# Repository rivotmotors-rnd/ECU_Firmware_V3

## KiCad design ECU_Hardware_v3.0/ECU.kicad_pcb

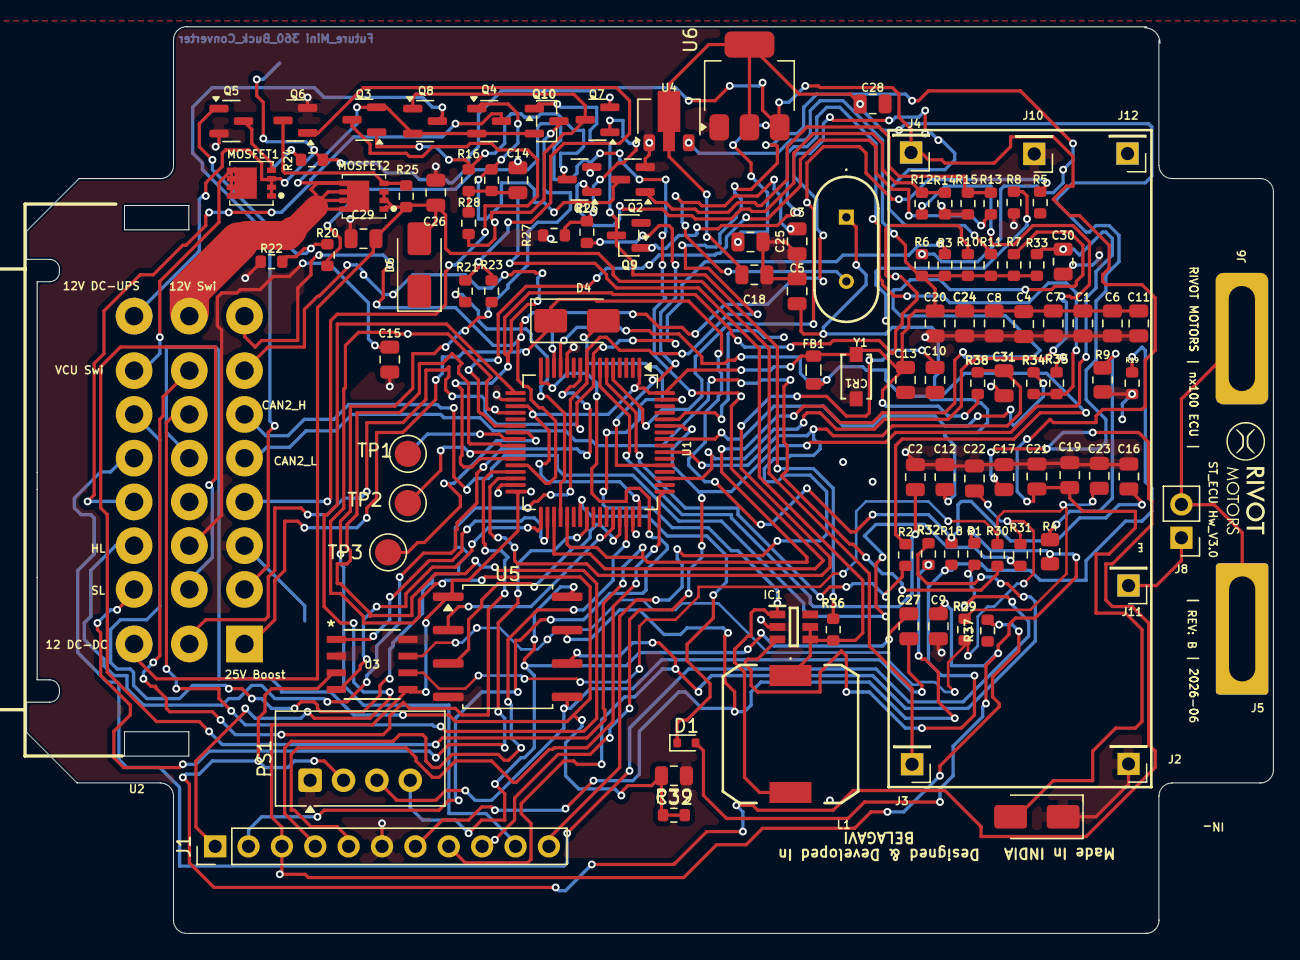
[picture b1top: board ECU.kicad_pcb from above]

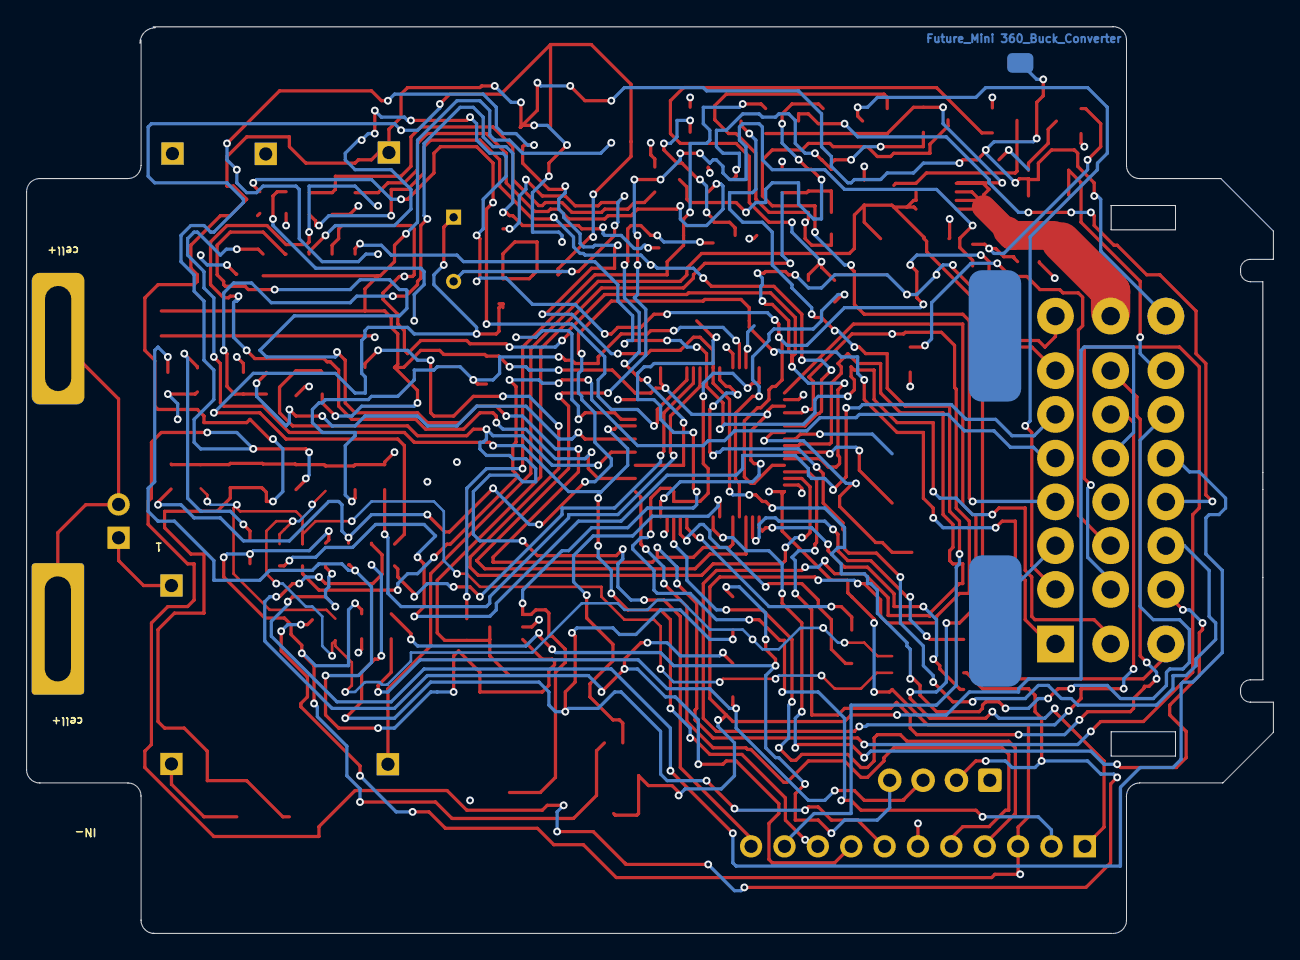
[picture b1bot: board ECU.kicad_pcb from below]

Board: 2 copper layers, 94.9 x 69.0 mm, 114 parts (2 on the bottom side), 78 nets.

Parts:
C1: 10uF; C_0805_2012Metric
C2, C4, C6, C7, C8, C9, C11, C12, C15, C17, C19, C21, C22, C23, C26, C29, C30, C31, C32: 0.1uF; C_0805_2012Metric
C3, C5: 20pF; C_0805_2012Metric
C10: 4.7uF; C_0805_2012Metric
C13: 1uF; C_0805_2012Metric
C14, C16, C18, C20, C25, C28: 22uF; C_0805_2012Metric
C24, C27: 0.1 uF; C_0805_2012Metric
CR1: SMF3.3; CR_SOD-123FL_LTF
D1: 1N4148WT- 1V 50mA; D_SOD-523
D4: SS34; D_SMA
D5, D6: SMAJ13CA; D_SMA
FB1: 600R; L_0805_2012Metric
IC1: MT3608; SOT95P280X145-6N
J1: Conn_01x11; PinHeader_1x11_P2.54mm_Vertical
J2: IN -; PinHeader_1x01_P2.54mm_Vertical
J3: IN +; PinHeader_1x01_P2.54mm_Vertical
J4: DC UPS out; PinHeader_1x01_P2.54mm_Vertical
J5: Cell J1; PinHeader_1x01_P2.54mm_Vertical
J6: Cell J2; PinHeader_1x01_P2.54mm_Vertical
J8: Conn_01x02_Pin; PinHeader_1x02_P2.54mm_Vertical
J10: OUT -; PinHeader_1x01_P2.54mm_Vertical
J11: Bat +; PinHeader_1x01_P2.54mm_Vertical
J12: BAT -; PinHeader_1x01_P2.54mm_Vertical
J13, J14: BAT -; TestPoint_Pad_1.0x1.0mm
L1: 47uH CDRH104RT125NP; CDRH104RT125NP220MC
MOSFET1, MOSFET2: DMP3007SFG-7
PS1: B0505S-1W; Converter_DCDC_TRACO_TBA1-xxxx_THT
Q1, Q2, Q5, Q6, Q7, Q9: AO3400A; SOT-23
Q3, Q4, Q8, Q10: AO3401A; SOT-23
R1, R3, R6, R7, R8, R10, R11, R14, R15, R16, R17, R19, R22, R23, R24, R25, R27, R28, R35, R36: 10K; R_0603_1608Metric
R2, R5: 0R; R_0603_1608Metric
R4: 2.2K; R_0805_2012Metric
R9: 1.5K; R_0805_2012Metric
R12, R13, R20, R21, R26, R34: 1K; R_0603_1608Metric
R18: 390K; R_0603_1608Metric
R29, R32: 120R; R_0603_1608Metric
R30, R31: 0; R_0603_1608Metric
R33, R37, R38: 10k; R_0603_1608Metric
R39: 100; R_0603_1608Metric
TP1, TP2, TP3: TestPoint; TestPoint_Keystone_5000-5004_Miniature
U1: STM32F446RETx; LQFP-64_10x10mm_P0.5mm
U2: 针座灰DJ7241-1.5 2.8-10; CONN-TH_DJ7241-1.5-2.8-10
U3: TJA1051T/3/1J; SO8_SOT96-1_NXP
U4: HT7333-1-SOT89; SOT-89-3
U5: ISO1050DUB; SOP-8_6.62x9.15mm_P2.54mm
U6: AMS1117-5.0; SOT-223-3_TabPin2
Y1: Crystal; X49ST28000F20JGDTD

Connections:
12V DC UPS O/P: C19.2, C21.2, C25.2, D5.2 (A2), J4.1 (Pin_1_1), MOSFET1.1 (S), MOSFET1.2 (S), MOSFET1.3 (S), R24.2, U2.24, U6.3 (VI)
12V DC-DC: C26.2, C29.2, D6.2 (A2), J3.1 (Pin_1_1), MOSFET2.1 (S), MOSFET2.2 (S), MOSFET2.3 (S), R25.2, U2.17
12V_Swi_Con: C14.2, IC1.4 (EN), IC1.5 (IN), L1.1, MOSFET2.5 (D), MOSFET2.6 (D), MOSFET2.7 (D), MOSFET2.8 (D), Q3.2 (S), Q4.2 (S), Q8.2 (S), Q10.2 (S), R16.2, R17.2, R28.2, R36.2, U2.16
+3.3V: C1.2, C4.2, C6.2, C7.2, C8.2, C11.2, C13.2, C20.2, C24.1, CR1.2, FB1.2, J1.3, R3.2, R6.1, R7.2, R10.2, R11.1, R33.1, R37.2, R38.2, U1.1 (VBAT), U1.19 (VDD), U1.32 (VDD), U1.48 (VDD), U1.64 (VDD), U3.5 (VIO), U4.3 (VOUT), U5.1 (VCC1)
+3.3VA: C12.2, FB1.1, U1.13 (VDDA)
+5V: C17.2, C18.2, C28.2, PS1.2 (VIN), U3.3 (VCC), U4.2 (VIN), U6.2 (VO)
/BOOT0: R8.2, U1.60 (BOOT0)
/ESD Protection, TVS diode , low pass filter, 3.3 buck conversion/CAN_N: C23.2, R29.2, R30.1, U3.6 (CANL)
/ESD Protection, TVS diode , low pass filter, 3.3 buck conversion/CAN_P: C22.2, R29.1, R31.1, U3.7 (CANH)
AUX A: C31.2, J1.11, R38.1, U1.55 (PB3)
BAT +: J8.1, J11.1 (Pin_1_1)
Boost_25V_Controller: C16.2, D4.1 (K), R18.1, U2.1
Brake_Regen_IP: C15.2, R37.1, U1.14 (PA0), U2.11
Brake_Regen_Op: C32.2, R39.1, R39.2, U1.20 (PA4), U2.13
Btn_Hazardlight_IP: R7.1, U1.37 (PC6), U2.10
Btn_HighBeam_IP: R1.1, U2.21
Btn_LHIndicator_IP: R3.1, U1.8 (PC0), U2.9
Btn_OffIndicator_IP: R11.2, U1.28 (PB2), U2.8
Btn_RHIndicator_IP: R10.1, U1.27 (PB1), U2.7
Btn_Seatlock_IP: R6.2, U1.9 (PC1), U2.22
CAN1_H: J1.7, R32.1, U5.7 (CANH)
CAN1_L: J1.8, R32.2, U5.6 (CANL)
CAN2_RX: U1.33 (PB12), U3.4 (RXD)
CAN2_TX: U1.34 (PB13), U3.1 (TXD)
CANH: R31.2, U2.6
CANL: R30.2, U2.5
CP Detect_IP: C30.2, J1.9, R33.2, U1.59 (PB7)
CRX1: U1.44 (PA11), U5.2 (RXD)
CTX1: U1.45 (PA12), U5.3 (TXD)
Contactor Pin 12V+: J1.10, Q10.3 (D)
Contactor_Sig_OP: R34.1, U1.57 (PB5)
HndlLock_Sig_OP: U1.10 (PC2), U2.19
LH_Indicator_Sig_Con: Q3.3 (D), U2.4
LH_Indicator_Sig_OP: R12.1, U1.51 (PC10)
MCU_U2DEBUG_RX: J1.1, U1.17 (PA3)
MCU_U2DEBUG_TX: J1.2, U1.16 (PA2)
MCU_UART3_RX: U1.25 (PC5), U2.14
MCU_UART3_TX: U1.29 (PB10), U2.15
unnamed: C3.2, R5.1, Y1.2
unnamed: C5.2, R2.1, Y1.1
unnamed: C9.1, D1.2 (A), R1.2, R4.1
unnamed: D1.1 (K), U1.39 (PC8)
unnamed: D4.2 (A), IC1.1 (SW), L1.2
unnamed: IC1.3 (FB), R18.2, R19.2
unnamed: J5.1 (Pin_1_1), J6.1 (Pin_1_1), J8.2
unnamed: MOSFET1.4 (G), Q5.3 (D), R24.1
unnamed: MOSFET2.4 (G), Q6.3 (D), R25.1
unnamed: C27.2, PS1.3 (0V), U5.5 (GND2)
unnamed: C27.1, PS1.4 (+VO), U5.8 (VCC2)
unnamed: Q1.3 (D), Q3.1 (G), R16.1
unnamed: Q1.1 (G), R12.2, R14.1
unnamed: Q2.3 (D), Q4.1 (G), R17.1
unnamed: Q2.1 (G), R13.2, R15.1
unnamed: Q5.1 (G), R20.2, R22.1
unnamed: Q6.1 (G), R21.2, R23.1
unnamed: Q7.3 (D), Q8.1 (G), R28.1
unnamed: Q7.1 (G), R26.2, R27.1
unnamed: Q9.1 (G), R34.2, R35.1
unnamed: Q9.3 (D), Q10.1 (G), R36.1
unnamed: R4.2, R9.1
unnamed: C2.2, U1.7 (NRST)
unnamed: TP3.1 (1_1), U1.23 (PA7)
unnamed: TP2.1 (1_1), U1.26 (PB0)
unnamed: TP1.1 (1_1), U1.24 (PC4)
unnamed: R5.2, U1.5 (PH0)
unnamed: R2.2, U1.6 (PH1)
unnamed: C10.1, U1.30 (VCAP_1)
OUT -: C1.1, C2.1, C3.1, C4.1, C5.1, C6.1, C7.1, C8.1, C9.2, C10.2, C11.1, C12.1, C13.1, C14.1, C15.1, C16.1, C17.1, C18.1, C19.1, C20.1, C21.1, C22.1, C23.1, C24.2, C25.1, C26.1, C28.1, C29.1, C30.1, C31.1, C32.1, CR1.1, D5.1 (A1), D6.1 (A1), IC1.2 (GND), J1.6, J2.1 (Pin_1_1), J10.1 (Pin_1_1), J12.1 (Pin_1_1), J13.1 (Pin_1_1), J14.1 (Pin_1_1), PS1.1 (GND), Q1.2 (S), Q2.2 (S), Q5.2 (S), Q6.2 (S), Q7.2 (S), Q9.2 (S), R8.1, R9.2, R14.2, R15.2, R19.1, R22.2, R23.2, R27.2, R35.2, U1.12 (VSSA), U1.18 (VSS), U1.31 (VSS), U1.47 (VSS), U1.63 (VSS), U2.3, U3.2 (GND), U3.8 (S), U4.1 (GND), U5.4 (GND1), U6.1 (GND)
RH_Indicator_Sig_Con: Q8.3 (D), U2.2
RH_Indicator_Sig_OP: R26.1, U1.53 (PC12)
SWCLK: J1.5, U1.49 (PA14)
SWIO: J1.4, U1.46 (PA13)
SeatLock_Sig_OP: U1.40 (PC9), U2.18
Switching_12V: R21.1, U1.36 (PB15)
Tail-lamp_Sig_Con: Q4.3 (D), U2.20
Tail-lamp_Sig_OP: R13.1, U1.22 (PA6)
VCU_Sig_Con: MOSFET1.5 (D), MOSFET1.6 (D), MOSFET1.7 (D), MOSFET1.8 (D), U2.23
VCU_Sig_OP: R20.1, U1.35 (PB14)

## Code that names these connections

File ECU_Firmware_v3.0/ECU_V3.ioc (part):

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Mcu.Name=STM32F446R(C-E)Tx
Mcu.Package=LQFP64
Mcu.UserName=STM32F446RETx
PA11.Mode=CAN_Activate
PA11.Signal=CAN1_RX
PA12.Mode=CAN_Activate
PA12.Signal=CAN1_TX
PA13.Mode=Serial_Wire
PA13.Signal=SYS_JTMS-SWDIO
PA14.Mode=Serial_Wire
PA14.Signal=SYS_JTCK-SWCLK
PA0.GPIOParameters=GPIO_PuPd,GPIO_Label
PA0.GPIO_Label=BRAKE_INP
PA0.GPIO_PuPd=GPIO_PULLUP
PA0.Signal=GPIO_Input
PA2.Mode=Asynchronous
PA2.Signal=USART2_TX
PA3.Mode=Asynchronous
PA3.Signal=USART2_RX
PA4.Mode=DAC_OUT1
PA4.Signal=COMP_DAC1_group
PA6.GPIOParameters=GPIO_Label
PA6.GPIO_Label=TAIL_LAMP
PA6.Signal=GPIO_Output
PB1.GPIOParameters=GPIO_PuPd,GPIO_Label
PB1.GPIO_Label=RIGHT_IND_SW
PB1.GPIO_PuPd=GPIO_PULLUP
PB1.Signal=GPIO_Input
PB10.Mode=Asynchronous
PB10.Signal=USART3_TX
PB12.Mode=CAN_Activate
PB12.Signal=CAN2_RX
PB13.Mode=CAN_Activate
PB13.Signal=CAN2_TX
PB14.GPIOParameters=PinState,GPIO_Label
PB14.GPIO_Label=VCU_PWR
PB14.PinState=GPIO_PIN_SET
PB14.Signal=GPIO_Output
PB15.GPIOParameters=PinState,GPIO_Label
PB15.GPIO_Label=AUX_12V_EN
PB15.PinState=GPIO_PIN_RESET
PB15.Signal=GPIO_Output
PB2.GPIOParameters=GPIO_PuPd,GPIO_Label
PB2.GPIO_Label=OFF_INDICATOR_INP
PB2.GPIO_PuPd=GPIO_PULLUP
PB2.Signal=GPIO_Input
PB3.GPIOParameters=GPIO_PuPd,GPIO_Label
PB3.GPIO_Label=CONTACTOR_FEEDBACK
PB3.GPIO_PuPd=GPIO_PULLUP
PB3.Signal=GPIO_Input
PB5.GPIOParameters=GPIO_Label
PB5.GPIO_Label=HV_CONTACTOR
PB5.Signal=GPIO_Output
PB7.GPIOParameters=GPIO_PuPd,GPIO_Label,GPIO_Mode
PB7.GPIO_Label=CP_LINE_DETECT_Pin
PB7.GPIO_Mode=GPIO_MODE_INPUT
PB7.GPIO_PuPd=GPIO_PULLUP
PB7.Signal=GPIO_Input
PC0.GPIOParameters=GPIO_PuPd,GPIO_Label
PC0.GPIO_Label=LEFT_IND_SW
PC0.GPIO_PuPd=GPIO_PULLUP
PC0.Signal=GPIO_Input
PC1.GPIOParameters=GPIO_PuPd,GPIO_Label
PC1.GPIO_Label=SEAT_BTN
PC1.GPIO_PuPd=GPIO_PULLUP
PC1.Signal=GPIO_Input
PC10.GPIOParameters=GPIO_Label
PC10.GPIO_Label=LEFT_IND_LAMP
PC10.Signal=GPIO_Output
PC12.GPIOParameters=GPIO_Label
PC12.GPIO_Label=RIGHT_IND_LAMP
PC12.Signal=GPIO_Output
PC2.GPIOParameters=GPIO_Label
PC2.GPIO_Label=HANDLE_LOCK
PC2.Signal=GPIO_Output
PC5.Mode=Asynchronous
PC5.Signal=USART3_RX
PC6.GPIOParameters=GPIO_PuPd,GPIO_Label
PC6.GPIO_Label=HAZARD_SW
PC6.GPIO_PuPd=GPIO_PULLUP
PC6.Signal=GPIO_Input
PC8.GPIOParameters=GPIO_PuPd,GPIO_Label
PC8.GPIO_Label=HIGH_BEAM_SENSE
PC8.GPIO_PuPd=GPIO_PULLDOWN
PC8.Signal=GPIO_Input
PC9.GPIOParameters=GPIO_Label
PC9.GPIO_Label=SEAT_LOCK
PC9.Signal=GPIO_Output
PH0-OSC_IN.Mode=HSE-External-Oscillator
PH0-OSC_IN.Signal=RCC_OSC_IN
PH1-OSC_OUT.Mode=HSE-External-Oscillator
PH1-OSC_OUT.Signal=RCC_OSC_OUT
RCC.HSE_VALUE=8000000
RCC.SYSCLKFreq_VALUE=90000000
RCC.SYSCLKSource=RCC_SYSCLKSOURCE_PLLCLK
board=custom

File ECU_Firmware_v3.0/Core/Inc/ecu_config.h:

#ifndef ECU_CONFIG_H
#define ECU_CONFIG_H

#include "stm32f4xx_hal.h"

// =============================================================================
// 1. COMMUNICATION BUSES (UART & CAN)
// =============================================================================

// VCU UART (USART3 - Communication with Android VCU)
#define VCU_TX_PIN                  GPIO_PIN_10
#define VCU_TX_PORT                 GPIOB       // PB10
#define VCU_RX_PIN                  GPIO_PIN_5
#define VCU_RX_PORT                 GPIOC       // PC5
#define VCU_UART_AF                 GPIO_AF7_USART3

// Backward-compatibility aliases for VCU UART
#define VCU_TX_Pin                  VCU_TX_PIN
#define VCU_TX_GPIO_Port            VCU_TX_PORT
#define VCU_RX_Pin                  VCU_RX_PIN
#define VCU_RX_GPIO_Port            VCU_RX_PORT

// Debug UART (USART2 - ST-Link Virtual COM Port / Debug printf)
#define DEBUG_UART_TX_PIN           GPIO_PIN_2
#define DEBUG_UART_TX_PORT          GPIOA       // PA2
#define DEBUG_UART_RX_PIN           GPIO_PIN_3
#define DEBUG_UART_RX_PORT          GPIOA       // PA3
#define DEBUG_UART_AF               GPIO_AF7_USART2

// CAN Bus (CAN2 - Vehicle CAN Network)
#define CAN2_RX_PIN                 GPIO_PIN_12
#define CAN2_RX_PORT                GPIOB       // PB12
#define CAN2_TX_PIN                 GPIO_PIN_13
#define CAN2_TX_PORT                GPIOB       // PB13
#define CAN2_AF                     GPIO_AF9_CAN2

// Backward-compatibility aliases for CAN2
#define CAN2_RX_Pin                 CAN2_RX_PIN
#define CAN2_TX_Pin                 CAN2_TX_PIN
#define CAN2_GPIO_Port              CAN2_RX_PORT

// =============================================================================
// 2. POWER & SWITCHING (MOSFET CONTROL)
// =============================================================================

// 12V Main Load Switching MOSFET
#define SWITCHING_12V_PIN           GPIO_PIN_15
#define SWITCHING_12V_PORT          GPIOB       // PB15
#define SWITCHING_12V               SWITCHING_12V_PIN

// 12V VCU Power / Signal MOSFET
#define VCU_SIG_OP_PIN              GPIO_PIN_14
#define VCU_SIG_OP_PORT             GPIOB       // PB14
#define VCU_SIG_OP                  VCU_SIG_OP_PIN

// =============================================================================
// 3. ACTUATORS & LOCKS
// =============================================================================

// Handlebar Steering Lock (Single-wire DWT Pulse Protocol)
#define HNDLLOCK_SIG_OP_PIN         GPIO_PIN_2
#define HNDLLOCK_SIG_OP_PORT        GPIOC       // PC2

// Seat Latch Solenoid (Pulse Actuation)
#define SEATLOCK_SIG_OP_PIN         GPIO_PIN_9
#define SEATLOCK_SIG_OP_PORT        GPIOC       // PC9

// =============================================================================
// 4. LIGHTING OUTPUTS
// =============================================================================

// Left Turn Indicator Lamp
#define LH_INDICATOR_SIG_OP_PIN     GPIO_PIN_10
#define LH_INDICATOR_SIG_OP_PORT    GPIOC       // PC10
#define LH_INDICATOR_SIG_OP         LH_INDICATOR_SIG_OP_PIN

// Right Turn Indicator Lamp
#define RH_INDICATOR_SIG_OP_PIN     GPIO_PIN_12
#define RH_INDICATOR_SIG_OP_PORT    GPIOC       // PC12
#define RH_INDICATOR_SIG_OP         RH_INDICATOR_SIG_OP_PIN

// Tail Lamp / Backlight Output
#define TAIL_LAMP_SIG_OP_PIN        GPIO_PIN_6
#define TAIL_LAMP_SIG_OP_PORT       GPIOA       // PA6
#define TAIL_LAMP_SIG_OP            TAIL_LAMP_SIG_OP_PIN

// =============================================================================
// 5. VEHICLE INPUTS & SWITCHES
// =============================================================================

// Push-to-Off Digital Brake Switch (PA0, internal pull-up)
// Released at rest (contacts closed to GND) -> LOW (0V)
// Pulled / engaged (contacts open, pulled to 3.3V) -> HIGH (3.3V)
#define BRAKE_INP_PIN               GPIO_PIN_0
#define BRAKE_INP_PORT              GPIOA       // PA0
#define BRAKE_INP                   BRAKE_INP_PIN

// Contactor Weld Auxiliary Feedback (PB3, internal pull-up)
// Contactor OPEN: HIGH (safe)
// Contactor CLOSED/WELDED: LOW
#define CONTACTOR_FEEDBACK_PIN      GPIO_PIN_3
#define CONTACTOR_FEEDBACK_PORT     GPIOB       // PB3

// CP Line Gun Detect (PB7, internal pull-up)
// Gun Connected: LOW
// Gun Disconnected: HIGH
#define CP_LINE_DETECT_PIN          GPIO_PIN_7
#define CP_LINE_DETECT_PORT         GPIOB       // PB7

// Left Turn Indicator Switch
#define LEFT_INDICATOR_INP_PIN      GPIO_PIN_0
#define LEFT_INDICATOR_INP_PORT     GPIOC       // PC0
#define LEFT_INDICATOR_INP          LEFT_INDICATOR_INP_PIN

// Right Turn Indicator Switch
#define RIGHT_INDICATOR_INP_PIN     GPIO_PIN_1
#define RIGHT_INDICATOR_INP_PORT    GPIOB       // PB1
#define RIGHT_INDICATOR_INP         RIGHT_INDICATOR_INP_PIN

// Off / Kill Switch
#define OFF_INDICATOR_INP_PIN       GPIO_PIN_2
#define OFF_INDICATOR_INP_PORT      GPIOB       // PB2
#define OFF_INDICATOR_INP           OFF_INDICATOR_INP_PIN

// Hazard Light Switch
#define HAZARD_INP_PIN              GPIO_PIN_6
#define HAZARD_INP_PORT             GPIOC       // PC6
#define HAZARDAS                    HAZARD_INP_PIN

// Seat Latch Push Button
#define BUTTON_LOCK_PIN             GPIO_PIN_1
#define BUTTON_LOCK_PORT            GPIOC       // PC1

// High Beam / Ignition Status Sense
#define HIGH_BEAM_PIN               GPIO_PIN_8
#define HIGH_BEAM_PORT              GPIOC       // PC8

// =============================================================================
// 6. REGENERATIVE BRAKING ANALOG OUTPUT (DAC)
// =============================================================================

// Regenerative Braking Signal to Motor Controller (PA4 -> LM358 Buffer)
#define BRAKE_REGEN_DAC_PIN         GPIO_PIN_4
#define BRAKE_REGEN_DAC_PORT        GPIOA       // PA4
#define BRAKE_REGEN_DAC_CH          DAC_CHANNEL_1

// 12-bit DAC Counts for 3.3V VREF: (Target_Voltage / 3.3V) * 4095
// Brake Released: 0.8V -> (0.8 / 3.3) * 4095 = 993 counts
// Brake Pulled:   2.5V -> (2.5 / 3.3) * 4095 = 3102 counts
#define BRAKE_REGEN_DAC_VAL_RELEASED 993U
#define BRAKE_REGEN_DAC_VAL_PULLED   3102U

#endif // ECU_CONFIG_H
